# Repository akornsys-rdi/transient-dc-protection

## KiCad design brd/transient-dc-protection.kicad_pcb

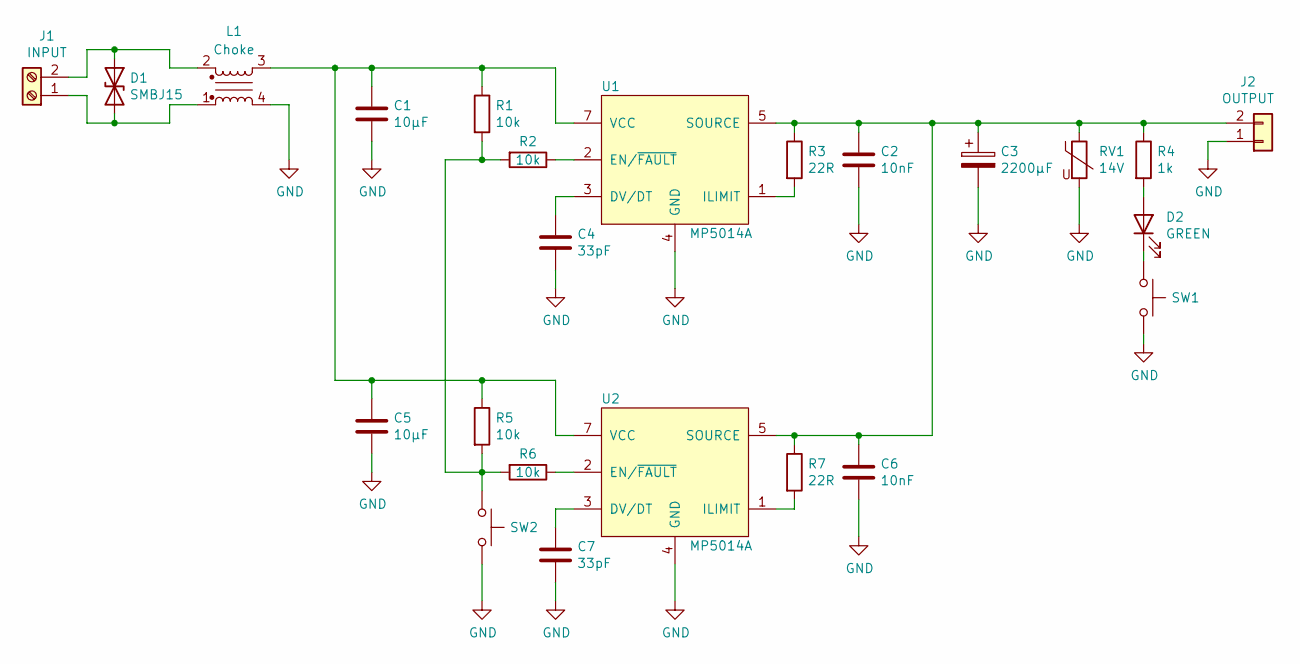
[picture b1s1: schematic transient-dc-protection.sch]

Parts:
C1, C5: 10µF; C_0805_2012Metric; Manufacturer Part Number CL21A106KAYNNNF
C2, C6: 10nF; C_0805_2012Metric; Manufacturer Part Number CC0805MRX7R9BB103
C3: 2200µF; CP_Radial_D12.5mm_P5.00mm; Manufacturer Part Number UHW1E222MHD
C4, C7: 33pF; C_0805_2012Metric; Manufacturer Part Number C0805C330J5GACTU
D1: SMBJ15; D_SMB; Manufacturer Part Number SMBJ15CA-13-F
D2: GREEN; LED_D3.0mm_Horizontal_O1.27mm_Z2.0mm; Manufacturer Part Number LTL-4232N
J1: INPUT; TerminalBlock_Phoenix_MKDS-3-2-5.08_1x02_P5.08mm_Horizontal; Manufacturer Part Number 1985946
J2: OUTPUT; SolderWire-2.5sqmm_1x02_P7.2mm_D2.4mm_OD3.6mm
L1: Choke; ECMS1V0704; Manufacturer Part Number ECMS1V0704-141-R
R1, R2, R5, R6: 10k; R_0805_2012Metric; Manufacturer Part Number CR0805-JW-103ELF
R3, R7: 22R; R_0805_2012Metric; Manufacturer Part Number RK73H2ATTDD22R0F
R4: 1k; R_0805_2012Metric; Manufacturer Part Number ERJ-P06J102V
RV1: 14V; RV_Disc_D12mm_W3.9mm_P7.5mm; Manufacturer Part Number B72210S1140K102
SW1, SW2: SW_Push; SW_Tactile_SPST_Angled_PTS645Vx58-2LFS; Manufacturer Part Number TS11-674-50-BK-100-RA-D
U1, U2: MP5014A; SOT-23-8; Manufacturer Part Number MP5014AGJ-P

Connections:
GND: C1.2, C2.2, C3.2, C4.2, C5.2, C6.2, C7.2, J2.1, L1.4, RV1.2, SW1.1, SW2.2, U1.4 (GND), U2.4 (GND)
unnamed: C2.1, C3.1, C6.1, J2.2, R3.1, R4.1, R7.1, RV1.1, U1.5 (SOURCE), U1.6 (SOURCE), U2.5 (SOURCE), U2.6 (SOURCE)
unnamed: C4.1, U1.3 (DV/DT)
unnamed: C7.1, U2.3 (DV/DT)
unnamed: D1.1 (A1), J1.2, L1.2
unnamed: D1.2 (A2), J1.1, L1.1
unnamed: D2.1 (K), SW1.2
unnamed: D2.2 (A), R4.2
unnamed: R1.2, R2.2, R5.2, R6.2, SW2.1
unnamed: R2.1, U1.2 (EN/~FAULT)
unnamed: R3.2, U1.1 (ILIMIT)
unnamed: R6.1, U2.2 (EN/~FAULT)
unnamed: R7.2, U2.1 (ILIMIT)
VCC: C1.1, C5.1, L1.3, R1.1, R5.1, U1.7 (VCC), U1.8 (VCC), U2.7 (VCC), U2.8 (VCC)

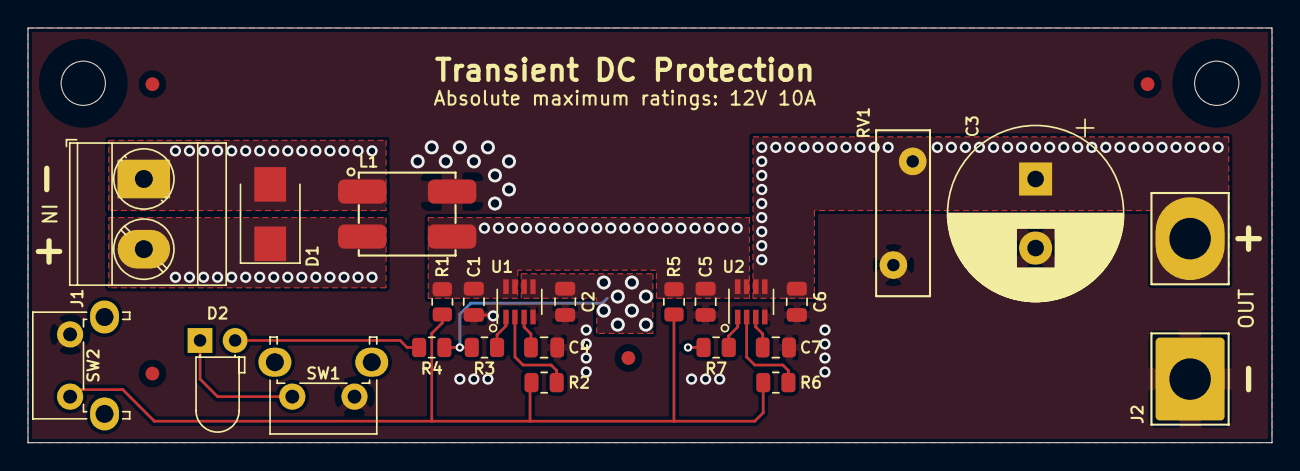
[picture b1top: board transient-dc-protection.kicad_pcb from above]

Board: 2 copper layers, 90.0 x 30.0 mm, 24 parts (0 on the bottom side), 14 nets.

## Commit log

2023-04-21 subida placa !WIP

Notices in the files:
brd/transient-dc-protection.kicad_pcb:
Copyright © 2023 RileyStarlight
Released under CERN OHL-S 2 License
https://cern-ohl.web.cern.ch
